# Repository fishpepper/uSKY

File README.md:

# uSKY -- the world's smallest and lightest (0.4g) Frsky compatible RC receiver

This is for educational use only, bad things could happen if you run this on a real vehicle. 
Its meant to be used on indoor and/or small vehicles.

see http://fishpepper.de/projects/uSKY for more info

This hardware design uses some very bad hacks to archive the small package size,
i would not recommend this to be used for a production run! Stick to the Application Notes from TI
if you want to build a commercial device based on this. This layout will probably not pass anc compliance
testing and depending on transmission laws in your country it is probably not allowed to be operated without further testing.

This work is published under the CERN open hardware license v1.2.
Feel free to use the design - but make sure to give proper credit and
release all modifications under the same license! See LICENSE.txt for details!

I AM NOT RESPONSIBLE FOR ANY DAMAGE/INJURIES CAUSED BY USING THIS DEVICE!

Make sure to init the git submodule for the libraries in kicad_misc by calling
git submodule init && git submodule update

enjoy!

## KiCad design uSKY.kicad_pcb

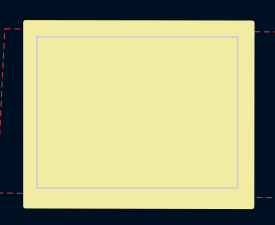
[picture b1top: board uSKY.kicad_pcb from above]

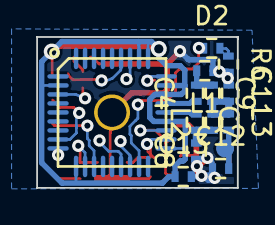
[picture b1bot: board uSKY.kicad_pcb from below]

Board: 2 copper layers, 11.2 x 8.4 mm, 35 parts (14 on the bottom side), 24 nets.

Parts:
3V3: TP; TP_1x1
ADC0, ADC1: TP; TP_1x1
ANT1: TP; smd_1x1_round
C1, C10: 1u; R_0402
C2, C6: 12p; R_0402
C3, C13: 100n; R_0402
C4, C7: 100p; R_0402
C5: 220p; R_0402
C8, C9: 1p; R_0402
C11: 1p8; R_0402
C12: 1p5; R_0402
D1, D2: LED; R_0402
DEBUG1: TP; TP_1x1
GND1: TP; TP_1x1
ISP_CLOCK1: TP; TP_1x1
ISP_DATA1: TP; TP_1x1
L1, L2, L3: 1.2nH; R_0402
R1: 5k6; R_0402
R2, R5: 10k; R_0402
R3: 56k; R_0402
R4, R6: 1k; R_0402
SBUS_PPM1: TP; TP_1x1
U1: CC2510; QFN36_CC2510_GNDPLANE_HACK
X1: SMD_CRYSTAL_4PIN; crystal_2016

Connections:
/ADC0: ADC0.1, U1.12
/ADC1: ADC1.1, R2.2
/ANT_N: C4.1, U1.24
/ANT_P: C7.1, U1.23
/DEBUG: DEBUG1.1, U1.8
/ISP_CLOCK: ISP_CLOCK1.1, U1.16
/ISP_DATA: ISP_DATA1.1, U1.15
/SBUS_PPM: SBUS_PPM1.1, U1.9
/~RESET: R5.2, U1.31
GND: C1.1, C2.2, C3.2, C5.2, C6.2, C8.1, C10.2, C11.1, C12.1, C13.2, GND1.1, L1.1, R1.2, R3.1, R4.2, R6.2, U1.GND, X1.2, X1.4
unnamed: ANT1.1, C12.2, L3.2
unnamed: C1.2, U1.30
unnamed: C2.1, U1.20, X1.1
unnamed: C4.2, C9.1, L1.2
unnamed: C6.1, U1.21, X1.3
unnamed: C7.2, C8.2, L2.1
unnamed: C9.2, C11.2, L2.2, L3.1
unnamed: D1.1, U1.3
unnamed: D1.2, R4.1
unnamed: D2.1, U1.17
unnamed: D2.2, R6.1
unnamed: R1.1, R2.1, U1.11
unnamed: R3.2, U1.27
VCC: 3V3.1, C3.1, C5.1, C10.1, C13.1, R5.1, U1.2, U1.10, U1.19, U1.22, U1.25, U1.26, U1.28, U1.29

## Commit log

2016-12-03 public release
2016-12-03 added submodule
2017-03-04 removed silkscreen filled zone
